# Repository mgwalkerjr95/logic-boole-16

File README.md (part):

<div align="center">

# Logic Boole 16

**An open-source logic analyzer on USB 3: 16 channels at 200 MS/s, or 4 at 750 MS/s.**<br>
It runs from one USB-C cable on a computer, or sits on a Raspberry Pi 4 or 5 as a HAT+.

**[Quick start](boards/v1.0.0/docs/quick-start.pdf)** · **[Datasheet](boards/v1.0.0/docs/datasheet.pdf)** · **[Software](software/README.md)** · **[FPGA design](gateware/README.md)** · **[Firmware](firmware/README.md)** · **[Protocol](docs/protocol.md)** · **[Schematic](boards/v1.0.0/hardware/logic-boole-16_revC_schematic.pdf)**

</div>

This repository holds everything for the board: the KiCad project and fabrication files, the FPGA design, the
firmware, and the software for the computer. The picture is a render of the design.

## Board versions

The version is printed on the back of the board. Each version keeps its own documents and design files in
[boards/](boards/). The software, the FPGA design, the firmware and the [protocol](docs/protocol.md) are shared.

| Version | On the back | Thresholds | Documents | Design files |
|---|---|---|---|---|
| **V1.0.0** (November 2026) | REV C · 2026 | 0.3 to 3 V | [Datasheet](boards/v1.0.0/docs/datasheet.pdf) · [Quick start](boards/v1.0.0/docs/quick-start.pdf) · [Schematic](boards/v1.0.0/hardware/logic-boole-16_revC_schematic.pdf) | [boards/v1.0.0/](boards/v1.0.0/) |

## What it does

| Feature | What you get |
|---|---|
| **16 channels at 200 MS/s** | Two pods of 8, a sample every 5 ns. Clocks up to 85 MHz are captured whole on every input |
| **8 channels at 375 MS/s, 4 at 750 MS/s** | A second FPGA design takes fewer channels more often: a sample every 1.33 ns with four, and clocks up to 200 MHz captured whole on every input. It samples and streams, with no trigger |
| **Two logic voltages in one capture** | A separate threshold for each pod, set from 0.3 V to 3 V |
| **A trigger in the FPGA** | Edges, levels, pulses by their length and levels that have lasted, up to four stages in turn, with a trigger input and a trigger output on a header |
| **Glitch filter and capture clock** | A filter for each channel up to 1.25 µs, and sampling on the circuit's own clock up to 50 MHz |
| **Streams to the host** | Samples go over USB 3 as they are taken, not into a small buffer on the board. The longest capture so far is 600 million samples |
| **Protected inputs** | 1 MΩ, with a comparator on every channel, designed for ±25 V |
| **One cable** | Power and data on USB-C, about 1 W |
| **Raspberry Pi HAT+** | Stacks on a Pi 4 or 5 with room for the Pi 5's Active Cooler. The Pi's own I²C, UART and SPI lines can take the place of pod channels, with no leads, once the board's solder jumpers are closed |
| **Nothing to brick** | The board keeps no firmware: the software loads it over USB each time it is plugged in |
| **Decoders, scripts and AI agents** | I²C, SPI and serial in the app, [sigrok](https://sigrok.org)'s decoders from the command line, a Python package, and an MCP server |

## The app

`logicboole` opens the app in your browser: waveforms, a threshold for each pod, the trigger, and decoders
for I²C, SPI and serial that it can find by itself. With a board on USB it opens on an empty scope: press Start.
With no board it shows its own simulated signals, under a strip marked SIMULATED, as in the picture.
`logicboole --fake` runs the whole software with a stand-in for the board.

## Get started

You need a Mac or a Linux computer (a Raspberry Pi 4 or 5 counts), Python 3.9 or later, and a USB 3 cable with
a USB-C plug for the board. A board comes with no cable, leads, spacers or screws.

**1. Install the software**

```sh
brew install pipx libusb    # macOS, with Homebrew
sudo apt install pipx       # Debian, Ubuntu, Raspberry Pi OS: libusb is there already
pipx ensurepath             # once; then open a new terminal window
pipx install logicboole
```

(`pip install logicboole` in a virtual environment does the same.) On Linux, the first `logicboole check` with
the board plugged in prints one line of commands that installs the USB rule, so that the board can be used
without `sudo`: run it once. To update the software later: `pipx upgrade logicboole`. A board that stayed
plugged in meanwhile is loaded with the new firmware and FPGA design by the next command, which says so.

From a copy of this repository nothing needs installing: `./logicboole`, in its top folder, does what
`logicboole` does here.

**2. Plug the board in and check it**

```sh
logicboole check
```

This checks the computer and the board in a few seconds and says what to do about anything that is missing.
The first time it loads a board, the software downloads the FX3's firmware image (about 110 kB), checks it and
keeps it: that once, the computer needs a connection to the internet.

**3. Capture**

```sh
# The app, in your browser
logicboole

# A capture into two files, the app's own and one for PulseView, with a threshold for each pod
logicboole capture bus.lb16 bus.sr --rate 10M --time 2 -a 1.65 -b 0.9

# Wait up to 10 seconds for B0 to fall, and keep the millisecond after it
logicboole capture reset.sr --rate 200M --time 1ms --trigger "B0=f" --timeout 10

# What is on each channel: I2C, SPI, serial, a clock, PWM
logicboole detect bus.lb16

# What a protocol decoder finds in a saved capture
logicboole decode bus.lb16 i2c scl=A1 sda=A0

# Periods, frequencies and pulse lengths
logicboole measure bus.lb16

# Every low pulse on A0 of 500 ns or less (a sample is 100 ns at 10 MS/s), and a picture of a part of the capture
logicboole find bus.lb16 "A0=0 pulse ..500ns"
logicboole plot bus.lb16 --from 1ms --to 1.2ms
```

While the board waits for its trigger, `capture` prints
`Waiting for the trigger (B0=f), 10 s at the most.  Ctrl-C stops.` Ctrl-C ends the wait early. If the trigger
does not come, the file holds the last samples the board saw, the command says `NOT TRIGGERED`, and it exits with
status 3.

Captures are saved for PulseView (`.sr`), a waveform viewer (`.vcd`), a spreadsheet (`.csv`), or as the app's own
`.lb16`; the commands that read captures read `.lb16` and `.sr`. The decoders are sigrok's, more than a hundred of
them, run through `sigrok-cli` if it is installed. When something does not work,
[docs/troubleshooting.md](docs/troubleshooting.md) goes through what to check. For help, write to
support@nearfieldsupply.com, or open an issue at https://github.com/mgwalkerjr95/logic-boole-16/issues.

> [!TIP]
> The [quick start guide](boards/v1.0.0/docs/quick-start.pdf) goes from the box to a first capture on two pages: where the
> cable and the probes go, and the steps in order. Connect ground first: join any pin of a pod's lower row to
> your circuit's ground.

**Scripts and AI agents.** `import logicboole` is a Python package that needs only libusb, and the commands
print JSON with `--json`. An AI agent can use the board by itself: through the command line with the skill file
(`logicboole skill --install` puts it where Claude Code finds it), or through `logicboole mcp`, a Model Context
Protocol server.
[software/README.md](software/README.md) has every command, the triggers, the Python package, and setting up
an agent.

## Specifications

The [datasheet](boards/v1.0.0/docs/datasheet.pdf) has the full tables, the pins, the dimensions and the limits.

| Item | Value |
|---|---|
| Channels | 16, in two keyed 2 × 8 pods. Every even pin is a ground |
| Sample rate | 200 MS/s on 16 channels, or 200 MS/s divided by a whole number. With the fast FPGA design: 375 MS/s on 8 channels (a pod), 750 MS/s on 4 |
| Fastest signal | Clocks up to 85 MHz and pulses down to 6 ns at 200 MS/s; clocks up to 200 MHz and pulses down to 2.5 ns at 750 MS/s |
| Logic levels | 1.2 to 5 V. Captured so far: 3.3 V and 5 V logic |
| Thresholds | 0.3 to 3.0 V in 0.764 mV steps, one for each pod |
| Inputs | 1 MΩ and 10 pF to ground, designed for ±25 V |
| Streaming, run-length format | 16 channels at 200 MS/s, for signals that change in up to 96 million samples a second |
| Streaming, raw format | 16 channels at 100 MS/s, any signal. At 200 MS/s, 892,928 samples. With the fast design, any signal: 4 channels at 750 MS/s, 8 at 375 or 16 at 187.5 |
| Before the trigger | The newest 8184 words: 16,368 samples in the raw format, far more on quiet signals |
| Trigger header | TRIG IN, and TRIG OUT 75 to 80 ns after the trigger sample |
| Host link | USB 3 at 5 Gbit/s. USB 2.0 works and carries a ninth as much |
| Power | 5 V from USB-C or the Pi's header, about 1 W |
| Size | 82 × 86 mm, four layers, parts on the top side only |
| Main parts | Spartan-6 XC6SLX9 FPGA, Infineon EZ-USB FX3, 16 fast comparators |

## Documentation

| Document | What is in it |
|---|---|
| [Quick start guide](boards/v1.0.0/docs/quick-start.pdf) | From the box to a first capture, on two pages |
| [Datasheet](boards/v1.0.0/docs/datasheet.pdf) | Specifications, pins, dimensions, typical uses, what has been measured and the known limits |
| [Software](software/README.md) | Every command, the triggers, file formats, the Python package, AI agents |
| [FPGA design](gateware/README.md) | What the design does, simulating it, building it, and the published bitstream |
| [Firmware](firmware/README.md) | Building the FX3's firmware, and where the firmware image comes from |
| [Troubleshooting](docs/troubleshooting.md) | What to check when the board is not found, a channel shows nothing, or a capture overflows |
| [Protocol](docs/protocol.md) | The USB requests, the FPGA's registers and the format of the sample stream |
| [Schematic](boards/v1.0.0/hardware/logic-boole-16_revC_schematic.pdf) | Eight sheets, as a PDF |

## What is here

| Path | What it is |
|---|---|
| `logicboole` | Runs the host software from this folder |
| `software/` | The host software: the app, the command line, the Python package, and the skill file and MCP server for AI agents, with the FPGA bitstream they load |
| `gateware/` | The FPGA's design in Verilog, its simulation, and the script that builds it with ISE 14.7 |
| `firmware/` | The FX3's firmware in C, built against Infineon's FX3 SDK |
| `docs/` | The protocol, troubleshooting, and the pictures on this page |
| `boards/` | A folder for each board version. What is in one: |
| `boards/v1.0.0/docs/` | The quick start guide and the datasheet, each as a PDF and as the page it is printed from |
| `boards/v1.0.0/hardware/kicad/` | The KiCad 10 project: schematic (8 sheets), board, design rules, and the symbols and two footprints that are not in KiCad's own libraries |
| `boards/v1.0.0/hardware/bom.csv` | Parts list: maker's part numbers, LCSC numbers, alternatives, and price and stock on the date given |
| `boards/v1.0.0/hardware/fabrication/` | Gerber and drill files (also zipped), and the parts list and placement file for JLCPCB |
| `boards/v1.0.0/hardware/3d/` | 3D model of the assembled board |
| `boards/v1.0.0/hardware/images/` | Renders of the [front](boards/v1.0.0/hardware/images/front.jpg) and the [back](boards/v1.0.0/hardware/images/back.jpg) |

## Changing it

- **The app and the command line** are plain Python and JavaScript with no build step: edit and run.
  [software/README.md](software/README.md) says what is in each file.
- **The FPGA's design** is simulated with Icarus Verilog (`sh gateware/sim.sh`) and built with ISE 14.7.
- **The firmware** is one C file, built with `make` against Infineon's SDK.
- **The hardware**: open `boards/v1.0.0/hardware/kicad/logic-boole-16.kicad_pro` in KiCad 10. The project carries its own
  symbol and footprint libraries; everything else comes from the libraries KiCad installs.
- `./logicboole load --gateware FILE.bin --firmware FILE.img` runs your build on the board, and
  `./logicboole selftest` then checks the path from the FPGA to the computer, every word compared. Nothing you
  load can brick the board: unplug it and plug it in again, and it is as it was.

## Making boards

<details>
<summary><b>Having boards made</b>: the stack-up, what the assembler places, and what is soldered by hand</summary>

<br>

The fabrication files are the ones V1.0.0 (revision C) was made from at JLCPCB.

**Bare board**

| Option | Value |
|---|---|
| Layers, thickness | 4 layers, 1.6 mm |
| Stack-up | JLC04161H-3313. The 90 Ω USB pairs and the 50 Ω lines are sized for it; another stack-up changes their impedance |
| Copper | 1 oz outer, 0.5 oz inner |
| Surface finish | ENIG, for the 0.8 mm BGA and the 0.5 mm pitch parts |
| Smallest features | 0.1 mm track and gap; vias with a 0.2 mm hole in a 0.45 mm pad |

**Assembly**

- Standard assembly, top side only. JLCPCB places 410 parts of 70 types.
- The FX3 (U12) is a BGA and needs X-ray inspection.
- JLCPCB leaves two matched lines unticked, and the boards come without them unless they are ticked: J1, the
  USB-C receptacle, and U3 and U4, the TPS62A02P regulators.
- Check stock of the input ESD diodes (ESD701DPYR, 16 a board) before ordering more than a few boards.

**By hand afterwards**

- J8, the 40-pin stacking header, is not in JLCPCB's library. It is a SparkFun PRT-16764, soldered square to
  the board after delivery.
- On a Raspberry Pi the board sits on four M2.5 × 16 mm spacers, held by eight M2.5 × 6 mm screws, which leaves
  room for the Pi 5's Active Cooler. Spacers and screws are not part of the board.

</details>

<details>
<summary><b>Parts notes</b>: the comparators, the positions left empty, and the programming connectors</summary>

<br>

- **Comparators.** U15 to U18, on pod A, are MX3502S; U19 to U22, on pod B, are TLV3502AIDR. The two parts are
  pin-compatible and either fits all eight positions. JLCPCB draws them a quarter turn apart, so check their
  rotation in the placement preview after changing one.
- **Positions left empty.** U13 takes an SPI flash and J3 a header for the FX3's serial port. They and a few
  resistors are marked "not fitted" in the parts list.
- **Programming connectors.** J2 (FX3) and J4 (FPGA) are Tag-Connect TC2050 footprints for the TC2050-IDC cable.
  They take no part.

</details>

## License

Copyright © 2026 Michael Walker.

| Part | License | Text |
|---|---|---|
| `boards/`, `gateware/`, `docs/`, and whatever is not named below | CERN-OHL-S v2 | [LICENSE](LICENSE) |
| `software/` and the `logicboole` launcher | GPL-3.0-or-later | [software/LICENSE](software/LICENSE) |
| `firmware/` | MIT | [firmware/LICENSE](firmware/LICENSE) |

**The hardware design and the FPGA design.** This source describes Open Hardware and is licensed under the
CERN-OHL-S v2. You may redistribute and modify this source and make products using it under the terms of the
CERN-OHL-S v2, in [LICENSE](LICENSE) and at https://ohwr.org/cern_ohl_s_v2.txt.

This source is distributed WITHOUT ANY EXPRESS OR IMPLIED WARRANTY, INCLUDING OF MERCHANTABILITY, SATISFACTORY
QUALITY AND FITNESS FOR A PARTICULAR PURPOSE. Please see the CERN-OHL-S v2 for applicable conditions.

**The host software** is free software: you can redistribute it and/or modify it under the terms of the GNU
General Public License as published by the Free Software Foundation, either version 3 of the License, or (at your
option) any later version. It is distributed in the hope that it will be useful, but WITHOUT ANY WARRANTY; without
even the implied warranty of MERCHANTABILITY or FITNESS FOR A PARTICULAR PURPOSE. See the GNU General Public
License for more details.

**The firmware's source** is under the MIT license.

**Two built files** are loaded into the board, and each comes under the terms of what it is built from, not
under the host software's:

- `software/logicboole/data/gateware.bin` is the FPGA design, built from `gateware/`: CERN-OHL-S v2.
- **The firmware image is not in this repository.** It is built from `firmware/firmware.c` with Infineon's EZ-USB
  FX3 SDK and also holds code of the SDK's libraries, which is Infineon's and stays under the license of
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
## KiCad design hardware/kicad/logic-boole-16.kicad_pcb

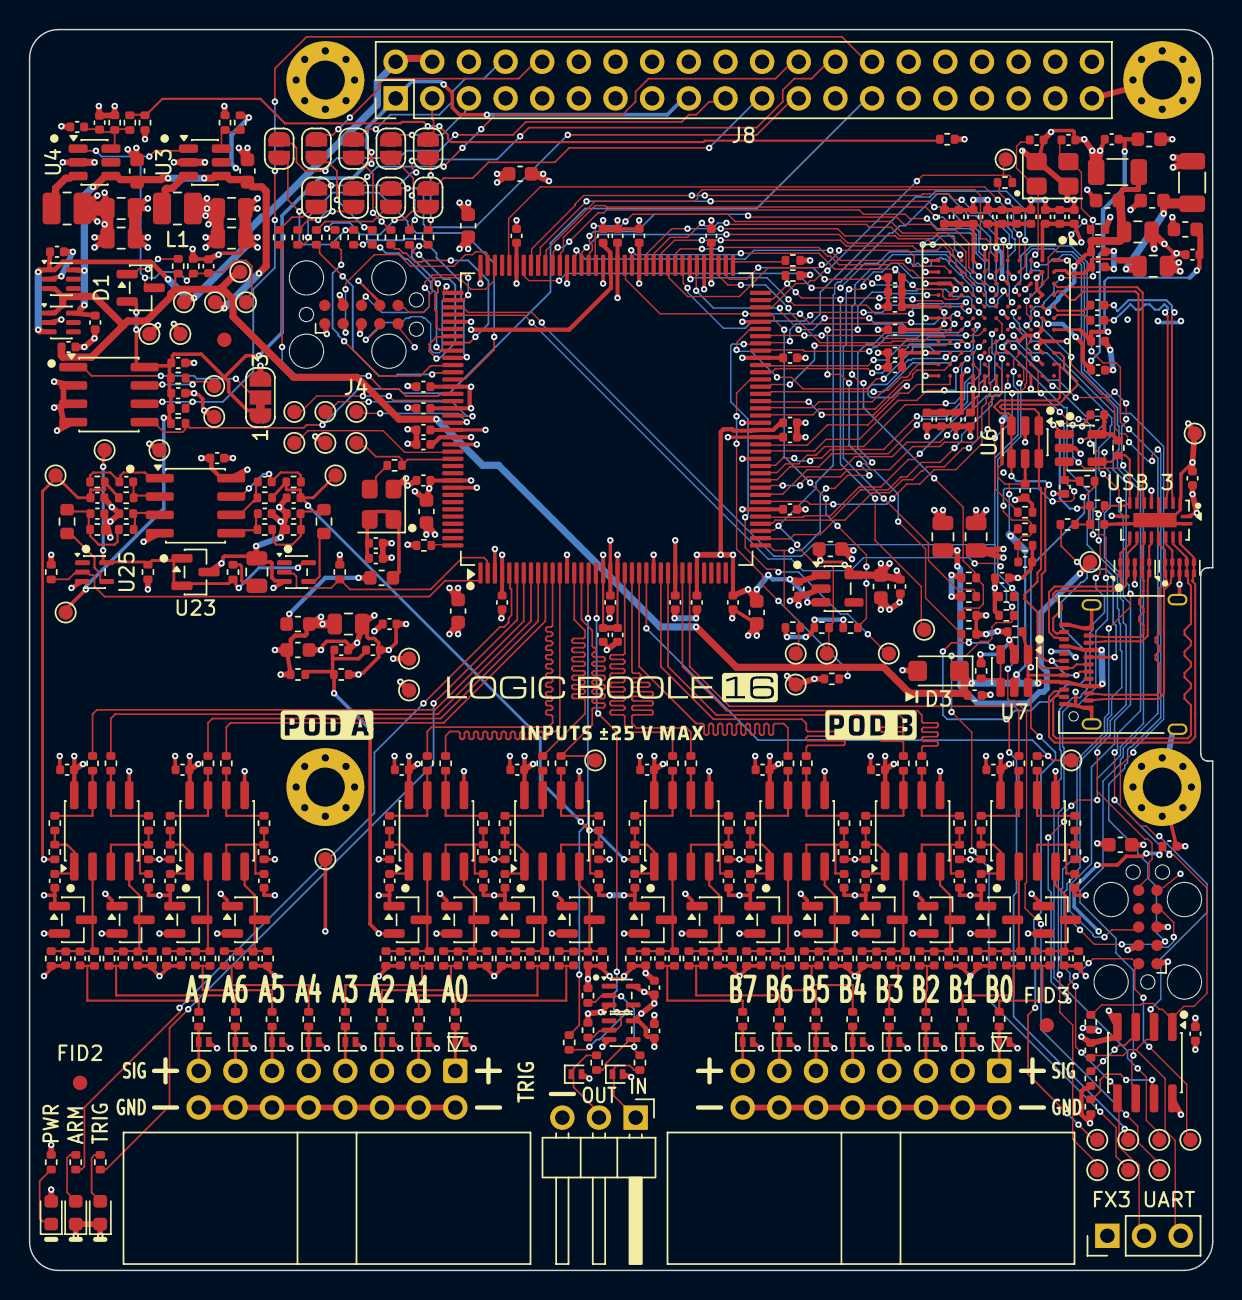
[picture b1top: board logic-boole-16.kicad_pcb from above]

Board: 4 copper layers, 82.0 x 86.0 mm, 477 parts (0 on the bottom side), 283 nets.

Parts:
C1, C10, C15, C58, C61, C90, C120, C154, C158, C159, C164: 1u; C_0402_1005Metric
C2, C12, C14, C18, C19, C20, C21, C24, C25, C26, C27, C28, C29, C35, C38, C41, C42, C44, C45, C47, C49, C51, C53, C55, C59, C60, C94, C101, C108, C115, C124, C131, C138, C145, C150, C151, C152, C155, C156, C160, C161, C162, C163: 100n; C_0402_1005Metric
C3, C16, C17, C30, C31, C32, C33, C43, C46, C48, C50, C52, C54, C153, C157: 10n; C_0402_1005Metric
C4, C7, C11, C62, C68, C74, C78, C82, C85: 4.7u; C_0603_1608Metric
C5, C6, C8, C9, C13, C149: 22u 10V; C_0805_2012Metric
C22, C23: 47u 6.3V; C_0805_2012Metric
C34: 2.2u; C_0402_1005Metric
C36, C39: 100u 6.3V; C_0805_2012Metric
C37, C40: 100u 6.3V; C_1206_3216Metric
C56, C57: 12p C0G; C_0402_1005Metric
C63, C64, C69, C70, C71, C72, C73, C75: 4.7u; C_0402_1005Metric
C65, C66, C67, C76, C77, C79, C80, C81, C83, C84, C86, C87, C88: 470n; C_0402_1005Metric
C89, C119: 10u; C_0603_1608Metric
C91, C95, C98, C102, C105, C109, C112, C116, C121, C125, C128, C132, C135, C139, C142, C146: 4.7p C0G +/-0.1pF; C_0402_1005Metric
C92, C96, C99, C103, C106, C110, C113, C117, C122, C126, C129, C133, C136, C140, C143, C147: 10p C0G 2%; C_0402_1005Metric
C93, C97, C100, C104, C107, C111, C114, C118, C123, C127, C130, C134, C137, C141, C144, C148: 47p C0G 5%; C_0402_1005Metric
C165, C166: 220p; C_0402_1005Metric
D1: BAT54C; SOT-23
D2: green (power); LED_0603_1608Metric
D3: SMF5.0A; D_SMF
D4: yellow (armed); LED_0603_1608Metric
D5: green (triggered / capturing); LED_0603_1608Metric
D6, D8, D10, D12, D14, D16, D18, D20, D22, D24, D26, D28, D30, D32, D34, D36: ESD701DPYR; D_SOD-882
D7, D9, D11, D13, D15, D17, D19, D21, D23, D25, D27, D29, D31, D33, D35, D37: BAV199; SOT-23
D38, D39: H5VL10B; D_SOD-882
FB1, FB2, FB5, FB6: 600R@100MHz; L_0603_1608Metric
FB3, FB4: 120R@100MHz; L_0603_1608Metric
FID1, FID2, FID3: Fiducial; Fiducial_1mm_Mask2mm
H1, H2, H3, H4: M2.5; MountingHole_2.7mm_M2.5_Pad_Via
J1: USB-C 24P (12401610E4#2A); USB_C_Receptacle_Amphenol_12401610E4-2A
J2: Tag-Connect TC2050 (ARM JTAG); Tag-Connect_TC2050-IDC-FP_2x05_P1.27mm_Vertical
J3: UART 1x3 2.54mm; PinHeader_1x03_P2.54mm_Vertical
J4: Tag-Connect TC2050 (Xilinx JTAG); Tag-Connect_TC2050-IDC-FP_2x05_P1.27mm_Vertical
J5: Pod A 2x8 box header (XY-IDC2.54-2*8P-W); IDC-Header_2x08_P2.54mm_Horizontal
J6: Pod B 2x8 box header (XY-IDC2.54-2*8P-W); IDC-Header_2x08_P2.54mm_Horizontal
J7: TRIG 1x3 2.54mm; PinHeader_1x03_P2.54mm_Horizontal
J8: 2x20 stacking header 13.5mm; PinHeader_2x20_P2.54mm_Vertical
JP1: ID addr 0x51 / 0x50; SolderJumper-3_P1.3mm_Bridged12_RoundedPad1.0x1.5mm_NumberL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
JP2: GPIO2 I2C1 SDA; SolderJumper-2_P1.3mm_Open_RoundedPad1.0x1.5mm
JP3: GPIO3 I2C1 SCL; SolderJumper-2_P1.3mm_Open_RoundedPad1.0x1.5mm
JP4: GPIO7 SPI0 CE1; SolderJumper-2_P1.3mm_Open_RoundedPad1.0x1.5mm
JP5: GPIO8 SPI0 CE0; SolderJumper-2_P1.3mm_Open_RoundedPad1.0x1.5mm
JP6: GPIO9 SPI0 MISO; SolderJumper-2_P1.3mm_Open_RoundedPad1.0x1.5mm
JP7: GPIO10 SPI0 MOSI; SolderJumper-2_P1.3mm_Open_RoundedPad1.0x1.5mm
JP8: GPIO11 SPI0 SCLK; SolderJumper-2_P1.3mm_Open_RoundedPad1.0x1.5mm
JP9: GPIO14 UART TXD; SolderJumper-2_P1.3mm_Open_RoundedPad1.0x1.5mm
JP10: GPIO15 UART RXD; SolderJumper-2_P1.3mm_Open_RoundedPad1.0x1.5mm
L1, L2: 1u 4A; L_1008_2520Metric
R1, R2, R10, R11, R137, R143, R152, R155: 100k; R_0402_1005Metric
R3, R12, R16, R17, R18, R19, R20, R22, R23, R24, R140, R142, R146, R148: 10k; R_0402_1005Metric
R4, R26, R27, R149: 2.2k; R_0402_1005Metric
R5, R6, R139, R145: 100k 0.1%; R_0402_1005Metric
R7, R30, R135: 330R; R_0402_1005Metric
R8, R9: 5.1k 1%; R_0402_1005Metric
R13: 10M; R_0402_1005Metric
R14: 6.04k 1%; R_0402_1005Metric
R15: 200R 1%; R_0402_1005Metric
R21: 15k; R_0402_1005Metric
R25: 2k; R_0402_1005Metric
R28, R29, R33: 4.7k; R_0402_1005Metric
R31, R32, R34, R42, R48, R54, R60, R66, R72, R78, R84, R90, R96, R102, R108, R114, R120, R126, R132, R150, R158, R159, R160, R161, R162, R163, R164, R165, R166, R167: 1k; R_0402_1005Metric
R35, R36, R153, R154: 33R; R_0402_1005Metric
R37, R38: 680R; R_0402_1005Metric
R39, R45, R51, R57, R63, R69, R75, R81, R87, R93, R99, R105, R111, R117, R123, R129, R151, R169: 100R; R_0402_1005Metric
R40, R46, R52, R58, R64, R70, R76, R82, R88, R94, R100, R106, R112, R118, R124, R130: 866k 1%; R_0402_1005Metric
R41, R47, R53, R59, R65, R71, R77, R83, R89, R95, R101, R107, R113, R119, R125, R131: 215k 1%; R_0402_1005Metric
R43, R49, R55, R61, R67, R73, R79, R85, R91, R97, R103, R109, R115, R121, R127, R133: 330k; R_0402_1005Metric
R44, R50, R56, R62, R68, R74, R80, R86, R92, R98, R104, R110, R116, R122, R128, R134, R141, R147: 22R; R_0402_1005Metric
R136: 1R 1%; R_0402_1005Metric
R138, R144: 301k 0.1%; R_0603_1608Metric
R156, R157: 3.9k; R_0402_1005Metric
R168: 0R; R_0402_1005Metric
TP1: VBUS; TestPoint_Pad_D1.0mm
TP2: PI_5V; TestPoint_Pad_D1.0mm
TP3: 5V; TestPoint_Pad_D1.0mm
TP4: BUCK_EN; TestPoint_Pad_D1.0mm
TP5: 3V3; TestPoint_Pad_D1.0mm
TP6: 3V3A; TestPoint_Pad_D1.0mm
TP7: 1V8; TestPoint_Pad_D1.0mm
TP8: 1V2; TestPoint_Pad_D1.0mm
TP9: PI_3V3; TestPoint_Pad_D1.0mm
TP10, TP11, TP12, TP30, TP36, TP39: GND; TestPoint_Pad_D1.0mm
TP13: CC1; TestPoint_Pad_D1.0mm
TP14: CC2; TestPoint_Pad_D1.0mm
TP15: SS_SEL; TestPoint_Pad_D1.0mm
TP16: FX3_RST; TestPoint_Pad_D1.0mm
TP17: SCL; TestPoint_Pad_D1.0mm
TP18: SDA; TestPoint_Pad_D1.0mm
TP19: FX3_TRST; TestPoint_Pad_D1.0mm
TP20: PROG_B; TestPoint_Pad_D1.0mm
TP21: INIT_B; TestPoint_Pad_D1.0mm
TP22: CCLK; TestPoint_Pad_D1.0mm
TP23: DIN; TestPoint_Pad_D1.0mm
TP24: DONE; TestPoint_Pad_D1.0mm
TP25: CLK24; TestPoint_Pad_D1.0mm
TP26: DBG0; TestPoint_Pad_D1.0mm
TP27: DBG1; TestPoint_Pad_D1.0mm
TP28: DBG2; TestPoint_Pad_D1.0mm
TP29: DBG3; TestPoint_Pad_D1.0mm
TP31: CHA0; TestPoint_Pad_D1.0mm
TP32: CHB0; TestPoint_Pad_D1.0mm
TP33: VREF; TestPoint_Pad_D1.0mm
TP34: VTH_A; TestPoint_Pad_D1.0mm
TP35: VTH_B; TestPoint_Pad_D1.0mm
TP37: VCLAMP; TestPoint_Pad_D1.0mm
TP38: ID_WP; TestPoint_Pad_D1.0mm
U1, U2: LM66100DCKR; SOT-363_SC-70-6
U3, U4: TPS62A02PDDCR; TSOT-23-6
U5: AP2112K-1.8TRG1; SOT-23-5
U6, U7: USBLC6-2SC6; SOT-23-6
U8, U9: TPD4EUSB30DQAR; USON-10_2.5x1.0mm_P0.5mm
U10: LMV331IDBVR; SOT-23-5
U11: HD3SS3212IRKSR; DHVQFN-20-1EP_2.5x4.5mm_P0.5mm_EP1x3mm
U12: CYUSB3014-BZXI; TFBGA-121_10x10mm_P0.8mm_FX3
U13: W25Q16JVSNIQ; SOIC-8_3.9x4.9mm_P1.27mm
U14: XC6SLX9-2TQG144C; TQFP-144_20x20mm_P0.5mm
U15, U16, U17, U18: MX3502S; SOIC-8_3.9x4.9mm_P1.27mm
U19, U20, U21, U22: TLV3502AIDR; SOIC-8_3.9x4.9mm_P1.27mm
U23: TL431BIDBZR; SOT-23
U24: TLV9062IDR; SOIC-8_3.9x4.9mm_P1.27mm
U25, U26, U27, U28: 74LVC1G17GW; SOT-353_SC-70-5
U29: M24C64-RMN6TP; SOIC-8_3.9x4.9mm_P1.27mm
Y1: 19.2MHz 12pF (X3225192MOB4SI); Crystal_SMD_3225-4Pin_3.2x2.5mm
Y2: 24MHz (OT2EL4C4JI-111OLP-24M); Oscillator_SMD_Abracon_ASE-4Pin_3.2x2.5mm

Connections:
+1V2: C8.1, C9.1, C22.1, C23.1, C24.1, C25.1, C26.1, C27.1, C28.1, C29.1, C30.1, C31.1, C32.1, C33.1, C62.1, C63.1, C64.1, C65.1, C66.1, C67.1, C165.2, FB2.1, FB3.1, FB4.1, L2.2, R168.1, R169.1, TP8.1, U12.B10 (VDD), U12.C3 (VDD), U12.E9 (VDD), U12.F11 (VDD), U12.H1 (VDD), U12.J11 (VDD), U12.L5 (VDD), U12.L7 (VDD), U14.19 (VCCINT), U14.28 (VCCINT), U14.52 (VCCINT), U14.89 (VCCINT), U14.128 (VCCINT)
+1V8: C11.1, C12.1, C44.1, C45.1, C46.1, C47.1, C48.1, C49.1, C50.1, C78.1, C79.1, C80.1, C81.1, C82.1, C83.1, C84.1, R16.1, R18.1, R28.1, R29.1, R30.1, R31.1, R32.1, TP7.1, U5.5 (VOUT), U12.E3 (VIO3), U12.F1 (VIO2), U12.H11 (VIO1), U12.L9 (VIO1), U14.42 (VCCO_2), U14.63 (VCCO_2), U14.76 (VCCO_1), U14.86 (VCCO_1), U14.103 (VCCO_1)
+3V3: C5.1, C6.1, C10.1, C18.1, C19.1, C51.1, C52.1, C53.1, C54.1, C59.1, C68.1, C69.1, C70.1, C71.1, C72.1, C73.1, C74.1, C75.1, C76.1, C77.1, C85.1, C86.1, C87.1, C88.1, C160.1, C161.1, D2.2 (A), FB1.1, FB5.1, FB6.1, J2.1 (VTref), J4.1, L1.2, R3.1, R12.1, R22.1, R23.1, R24.1, R26.1, R27.1, R33.1, TP5.1, U5.1 (VIN), U5.3 (EN), U10.5 (V+), U11.1 (NC/VCC), U11.6 (VCC), U11.10 (NC/VCC), U12.B1 (VIO4), U12.C11 (VIO5), U13.8 (VCC), U14.4 (VCCO_3), U14.18 (VCCO_3), U14.20 (VCCAUX), U14.31 (VCCO_3), U14.36 (VCCAUX), U14.53 (VCCAUX), U14.90 (VCCAUX), U14.122 (VCCO_0), U14.125 (VCCO_0), U14.129 (VCCAUX), U14.135 (VCCO_0), U27.5 (VCC), U28.5 (VCC)
+3V3A: C13.1, C14.1, C89.1, C94.1, C101.1, C108.1, C115.1, C119.1, C124.1, C131.1, C138.1, C145.1, C150.1, FB1.2, R135.1, R149.1, TP6.1, U15.8 (V+), U16.8 (V+), U17.8 (V+), U18.8 (V+), U19.8 (V+), U20.8 (V+), U21.8 (V+), U22.8 (V+), U24.8 (V+)
+5V: C2.1, C4.1, C7.1, TP3.1, U1.6 (VOUT), U2.6 (VOUT), U3.4 (VIN), U4.4 (VIN)
B1V2_FB: C165.1, C166.1, R5.2, R6.1, U4.6 (FB)
B1V2_SNS: R5.1, R168.2, R169.2
B1V2_SW: L2.1, U4.3 (SW)
B3V3_FB: R3.2, R4.1, U3.6 (FB)
B3V3_SW: L1.1, U3.3 (SW)
BUCK_EN: C3.1, D1.3, R2.1, TP4.1, U3.1 (EN), U4.1 (EN)
CC1_F: C16.1, R10.2, U10.3 (-)
CC2_F: C17.1, R11.2, R13.2, U10.1 (+)
CHA0: R44.2, TP31.1, U14.15 (IO_L44P_GCLK21_3)
CHA1: R50.2, U14.14 (IO_L44N_GCLK20_3)
CHA2: R56.2, U14.12 (IO_L49P_3)
CHA3: R62.2, U14.11 (IO_L49N_3)
CHA4: R68.2, U14.10 (IO_L50P_3)
CHA5: R74.2, U14.9 (IO_L50N_3)
CHA6: R80.2, U14.8 (IO_L51P_3)
CHA7: R86.2, U14.7 (IO_L51N_3)
CHB0: R92.2, TP32.1, U14.24 (IO_L41P_GCLK27_3)
CHB1: R98.2, U14.30 (IO_L36P_3)
CHB2: R104.2, U14.29 (IO_L36N_3)
CHB3: R110.2, U14.27 (IO_L37P_3)
CHB4: R116.2, U14.26 (IO_L37N_3)
CHB5: R122.2, U14.23 (IO_L41N_GCLK26_3)
CHB6: R128.2, U14.22 (IO_L42P_GCLK25_TRDY2_3)
CHB7: R134.2, U14.21 (IO_L42N_GCLK24_3)
CLK24: R36.2, TP25.1, U14.132 (IO_L35P_GCLK17_0)
CO_A0: R43.1, R44.1, U15.6 (OUTB)
CO_A1: R49.1, R50.1, U15.7 (OUTA)
CO_A2: R55.1, R56.1, U16.6 (OUTB)
CO_A3: R61.1, R62.1, U16.7 (OUTA)
CO_A4: R67.1, R68.1, U17.6 (OUTB)
CO_A5: R73.1, R74.1, U17.7 (OUTA)
CO_A6: R79.1, R80.1, U18.6 (OUTB)
CO_A7: R85.1, R86.1, U18.7 (OUTA)
CO_B0: R91.1, R92.1, U19.6 (OUTB)
CO_B1: R97.1, R98.1, U19.7 (OUTA)
CO_B2: R103.1, R104.1, U20.6 (OUTB)
CO_B3: R109.1, R110.1, U20.7 (OUTA)
CO_B4: R115.1, R116.1, U21.6 (OUTB)
CO_B5: R121.1, R122.1, U21.7 (OUTA)
CO_B6: R127.1, R128.1, U22.6 (OUTB)
CO_B7: R133.1, R134.1, U22.7 (OUTA)
EN_VBUS: D1.1, R1.2
FLASH_HOLD_N: R23.2, U13.7 (~HOLD/~RESET/IO_{3})
FLASH_WP_N: R22.2, U13.3 (~WP/IO_{2})
FPGA_CCLK: R35.2, TP22.1, U14.70 (IO_L1P_CCLK_2)
FPGA_DBG0: TP26.1, U14.124 (IO_L37P_GCLK13_0)
FPGA_DBG1: TP27.1, U14.126 (IO_L36N_GCLK14_0)
FPGA_DBG2: TP28.1, U14.127 (IO_L36P_GCLK15_0)
FPGA_DBG3: TP29.1, U14.131 (IO_L35N_GCLK16_0)
FPGA_DIN: TP23.1, U12.D2 (I2S_SD/GPIO51), U14.65 (IO_L3P_D0_DIN_MISO_MISO1_2)
FPGA_DONE: R30.2, TP24.1, U12.K5 (CTL10/GPIO27), U14.71 (DONE_2)
FPGA_HSWAPEN: R33.2, U14.144 (IO_L1P_HSWAPEN_0)
FPGA_INIT_B: R29.2, TP21.1, U12.F2 (GPIO45), U14.39 (IO_L65P_INIT_B_2)
FPGA_M0: R31.2, U14.69 (IO_L1N_M0_CMPMISO_2)
FPGA_M1: R32.2, U14.60 (IO_L13P_M1_2)
FPGA_PROGRAM_B: R28.2, TP20.1, U12.H6 (CTL9/GPIO26), U14.37 (PROGRAM_B_2)
FPGA_SUSPEND: R34.1, U14.73 (SUSPEND)
FPGA_TCK: J4.4, U14.109 (TCK)
FPGA_TDI: J4.8, U14.110 (TDI)
FPGA_TDO: J4.6, U14.106 (TDO)
FPGA_TMS: J4.2, U14.107 (TMS)
FX3_AVDD: C34.1, C35.1, FB2.2, U12.A7 (AVDD)
FX3_CTL0: U12.K8 (CTL0/GPIO17), U14.59 (IO_L13N_D10_2)
FX3_CTL1: U12.K7 (CTL1/GPIO18), U14.66 (IO_L2N_CMPMOSI_2)
FX3_CTL2: U12.J7 (CTL2/GPIO19), U14.75 (IO_L74P_AWAKE_1)
FX3_CTL3: U12.H7 (CTL3/GPIO20), U14.67 (IO_L2P_CMPCLK_2)
FX3_CTL4: U12.G7 (CTL4/GPIO21), U14.64 (IO_L3N_MOSI_CSI_B_MISO0_2)
FX3_CTL5: U12.G6 (CTL5/GPIO22), U14.74 (IO_L74N_DOUT_BUSY_1)
FX3_CTL6: U12.K6 (CTL6/GPIO23), U14.78 (IO_L47N_1)
FX3_CTL7: U12.H8 (CTL7/GPIO24), U14.62 (IO_L12P_D1_MISO2_2)
FX3_CTL8: U12.G5 (CTL8/GPIO25), U14.95 (IO_L40P_GCLK11_1)
FX3_CTL11: U12.J5 (CTL11/GPIO28), U14.80 (IO_L46N_1)
FX3_CTL12: U12.H5 (CTL12/GPIO29), U14.79 (IO_L47P_1)
FX3_CVDDQ: C42.1, C43.1, FB5.2, U12.B6 (CVDDQ)
FX3_DQ0: U12.F10 (DQ0/GPIO0), U14.38 (IO_L65N_CSO_B_2)
FX3_DQ1: U12.F9 (DQ1/GPIO1), U14.40 (IO_L64N_D9_2)
FX3_DQ2: U12.F7 (DQ2/GPIO2), U14.44 (IO_L62P_D5_2)
FX3_DQ3: U12.G10 (DQ3/GPIO3), U14.43 (IO_L62N_D6_2)
FX3_DQ4: U12.G9 (DQ4/GPIO4), U14.46 (IO_L49P_D3_2)
FX3_DQ5: U12.F8 (DQ5/GPIO5), U14.41 (IO_L64P_D8_2)
FX3_DQ6: U12.H10 (DQ6/GPIO6), U14.45 (IO_L49N_D4_2)
FX3_DQ7: U12.H9 (DQ7/GPIO7), U14.47 (IO_L48N_RDWR_B_VREF_2)
FX3_DQ8: U12.J10 (DQ8/GPIO8), U14.50 (IO_L31N_GCLK30_D15_2)
FX3_DQ9: U12.J9 (DQ9/GPIO9), U14.58 (IO_L14P_D11_2)
FX3_DQ10: U12.K11 (DQ10/GPIO10), U14.51 (IO_L31P_GCLK31_D14_2)
FX3_DQ11: U12.L10 (DQ11/GPIO11), U14.56 (IO_L30P_GCLK1_D13_2)
FX3_DQ12: U12.K10 (DQ12/GPIO12), U14.55 (IO_L30N_GCLK0_USERCCLK_2)
FX3_DQ13: U12.K9 (DQ13/GPIO13), U14.57 (IO_L14N_D12_2)
FX3_DQ14: U12.J8 (DQ14/GPIO14), U14.61 (IO_L12N_D2_MISO3_2)
FX3_DQ15: U12.G8 (DQ15/GPIO15), U14.48 (IO_L48P_D7_2)
FX3_DQ16: U12.K2 (DQ16/GPIO33), U14.82 (IO_L45N_1)
FX3_DQ17: U12.J4 (DQ17/GPIO34), U14.87 (IO_L42N_GCLK6_TRDY1_1)
FX3_DQ18: U12.K1 (DQ18/GPIO35), U14.83 (IO_L45P_1)
FX3_DQ19: U12.J2 (DQ19/GPIO36), U14.84 (IO_L43N_GCLK4_1)
FX3_DQ20: U12.J3 (DQ20/GPIO37), U14.81 (IO_L46P_1)
FX3_DQ21: U12.J1 (DQ21/GPIO38), U14.85 (IO_L43P_GCLK5_1)
FX3_DQ22: U12.H2 (DQ22/GPIO39), U14.93 (IO_L41P_GCLK9_IRDY1_1)
FX3_DQ23: U12.H3 (DQ23/GPIO40), U14.92 (IO_L41N_GCLK8_1)
FX3_DQ24: U12.F4 (DQ24/GPIO41), U14.98 (IO_L34P_1)
FX3_DQ25: U12.G2 (DQ25/GPIO42), U14.99 (IO_L33N_1)
FX3_DQ26: U12.G3 (DQ26/GPIO43), U14.94 (IO_L40N_GCLK10_1)
FX3_DQ27: U12.F3 (DQ27/GPIO44), U14.97 (IO_L34N_1)
FX3_DQ28: U12.F5 (DQ28/GPIO46), U14.100 (IO_L33P_1)
FX3_DQ29: U12.E1 (DQ29/GPIO47), U14.101 (IO_L32N_1)
FX3_DQ30: U12.E5 (DQ30/GPIO48), U14.104 (IO_L1N_VREF_1)
FX3_DQ31: U12.E4 (DQ31/GPIO49), U14.102 (IO_L32P_1)
FX3_I2S_CLK: R35.1, U12.D1 (I2S_CLK/GPIO50)
FX3_PCLK: U12.J6 (PCLK/GPIO16), U14.88 (IO_L42P_GCLK7_1)
FX3_PMODE0: R16.2, R17.1, U12.G4 (PMODE0/GPIO30)
FX3_PMODE1: R18.2, U12.H4 (PMODE1/GPIO31)
FX3_PMODE2: R19.1, U12.L4 (PMODE2/GPIO32)
FX3_RESET_N: C58.1, J2.10 (~RESET), R20.2, R21.1, TP16.1, U12.C5 (RESET#)
FX3_RUSB2: R14.1, U12.C8 (R_USB2)
FX3_RUSB3: R15.1, U12.B3 (R_USB3)
FX3_SCL: R26.2, TP17.1, U12.D9 (I2C_GPIO58/I2C_SCL), U14.111 (IO_L66N_SCP0_0)
FX3_SDA: R27.2, TP18.1, U12.D10 (I2C_GPIO59/I2C_SDA), U14.112 (IO_L66P_SCP1_0)
FX3_SPI_MISO: J3.3, R25.1, U12.C2 (UART_TX/SPI_MISO/GPIO55), U13.2 (DO/IO_{1})
FX3_SPI_MOSI: J3.2, U12.D5 (UART_RX/SPI_MOSI/GPIO56), U13.5 (DI/IO_{0})
FX3_SPI_SCK: U12.D4 (UART_RTS/SPI_SCK/GPIO53), U13.6 (CLK)
FX3_SPI_SSN: R24.2, U12.C1 (UART_CTS/SPI_SSN/GPIO54), U13.1 (~CS)
FX3_SSTX_N: C21.1, U12.A6 (SSTXM)
FX3_SSTX_P: C20.1, U12.A5 (SSTXP)
FX3_TCK: J2.4 (SWCLK/TCK), U12.F6 (TCK)
FX3_TDI: J2.8 (NC/TDI), U12.E7 (TDI)
FX3_TDO: J2.6 (SWO/TDO), U12.C10 (TDO)
FX3_TMS: J2.2 (SWDIO/TMS), U12.E8 (TMS)
FX3_TRST_N: TP19.1, U12.B11 (TRST#)
FX3_U3RX: C39.1, C40.1, C41.1, FB4.2, U12.A2 (U3RXVDDQ)
FX3_U3TX: C36.1, C37.1, C38.1, FB3.2, U12.B5 (U3TXVDDQ)
FX3_XI: C56.1, U12.C6 (XTALIN), Y1.1
FX3_XO: C57.1, U12.C7 (XTALOUT), Y1.3
GND: C1.2, C2.2, C3.2, C4.2, C5.2, C6.2, C7.2, C8.2, C9.2, C10.2, C11.2, C12.2, C13.2, C14.2, C15.2, C16.2, C17.2, C18.2, C19.2, C22.2, C23.2, C24.2, C25.2, C26.2, C27.2, C28.2, C29.2, C30.2, C31.2, C32.2, C33.2, C34.2, C35.2, C36.2, C37.2, C38.2, C39.2, C40.2, C41.2, C42.2, C43.2, C44.2, C45.2, C46.2, C47.2, C48.2, C49.2, C50.2, C51.2, C52.2, C53.2, C54.2, C55.2, C56.2, C57.2, C58.2, C59.2, C60.2, C61.2, C62.2, C63.2, C64.2, C65.2, C66.2, C67.2, C68.2, C69.2, C70.2, C71.2, C72.2, C73.2, C74.2, C75.2, C76.2, C77.2, C78.2, C79.2, C80.2, C81.2, C82.2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
ID_A0: JP1.2 (C), U29.1 (A0)
ID_SC: J8.28, R157.2, U29.6 (SCL)
ID_SD: J8.27, R156.2, U29.5 (SDA)
ID_WP: R158.2, TP38.1, U29.7 (WP)
INS_A0: C91.1, R39.2, R40.1
INS_A1: C95.1, R45.2, R46.1
INS_A2: C98.1, R51.2, R52.1
INS_A3: C102.1, R57.2, R58.1
INS_A4: C105.1, R63.2, R64.1
INS_A5: C109.1, R69.2, R70.1
INS_A6: C112.1, R75.2, R76.1
INS_A7: C116.1, R81.2, R82.1
INS_B0: C121.1, R87.2, R88.1
INS_B1: C125.1, R93.2, R94.1
INS_B2: C128.1, R99.2, R100.1
INS_B3: C132.1, R105.2, R106.1
INS_B4: C135.1, R111.2, R112.1
INS_B5: C139.1, R117.2, R118.1
INS_B6: C142.1, R123.2, R124.1
INS_B7: C146.1, R129.2, R130.1
IN_A0: D6.1 (A1), J5.1, R39.1
IN_A1: D8.1 (A1), J5.3, R45.1
IN_A2: D10.1 (A1), J5.5, R51.1
IN_A3: D12.1 (A1), J5.7, R57.1
IN_A4: D14.1 (A1), J5.9, R63.1
IN_A5: D16.1 (A1), J5.11, R69.1
IN_A6: D18.1 (A1), J5.13, R75.1
IN_A7: D20.1 (A1), J5.15, R81.1
IN_B0: D22.1 (A1), J6.1, R87.1
IN_B1: D24.1 (A1), J6.3, R93.1
IN_B2: D26.1 (A1), J6.5, R99.1
IN_B3: D28.1 (A1), J6.7, R105.1
IN_B4: D30.1 (A1), J6.9, R111.1
IN_B5: D32.1 (A1), J6.11, R117.1
IN_B6: D34.1 (A1), J6.13, R123.1
IN_B7: D36.1 (A1), J6.15, R129.1
LED_ARM: R37.1, U14.5 (IO_L52N_3)
LED_ARM_A: D4.2 (A), R37.2
LED_TRIG: R38.1, U14.6 (IO_L52P_3)
LED_TRIG_A: D5.2 (A), R38.2
ND_A0: C91.2, C92.1, D7.3 (COM), R40.2, R41.1, U15.4 (-INB)
ND_A1: C95.2, C96.1, D9.3 (COM), R46.2, R47.1, U15.2 (-INA)
ND_A2: C98.2, C99.1, D11.3 (COM), R52.2, R53.1, U16.4 (-INB)
ND_A3: C102.2, C103.1, D13.3 (COM), R58.2, R59.1, U16.2 (-INA)
ND_A4: C105.2, C106.1, D15.3 (COM), R64.2, R65.1, U17.4 (-INB)
ND_A5: C109.2, C110.1, D17.3 (COM), R70.2, R71.1, U17.2 (-INA)
ND_A6: C112.2, C113.1, D19.3 (COM), R76.2, R77.1, U18.4 (-INB)
ND_A7: C116.2, C117.1, D21.3 (COM), R82.2, R83.1, U18.2 (-INA)
ND_B0: C121.2, C122.1, D23.3 (COM), R88.2, R89.1, U19.4 (-INB)
ND_B1: C125.2, C126.1, D25.3 (COM), R94.2, R95.1, U19.2 (-INA)
ND_B2: C128.2, C129.1, D27.3 (COM), R100.2, R101.1, U20.4 (-INB)
ND_B3: C132.2, C133.1, D29.3 (COM), R106.2, R107.1, U20.2 (-INA)
ND_B4: C135.2, C136.1, D31.3 (COM), R112.2, R113.1, U21.4 (-INB)
ND_B5: C139.2, C140.1, D33.3 (COM), R118.2, R119.1, U21.2 (-INA)
ND_B6: C142.2, C143.1, D35.3 (COM), R124.2, R125.1, U22.4 (-INB)
ND_B7: C146.2, C147.1, D37.3 (COM), R130.2, R131.1, U22.2 (-INA)
PIF_GPIO2: R159.2, U14.114 (IO_L65N_SCP2_0)
PIF_GPIO3: R160.2, U14.115 (IO_L65P_SCP3_0)
PIF_GPIO7: R161.2, U14.123 (IO_L37N_GCLK12_0)
PIF_GPIO8: R162.2, U14.121 (IO_L62P_0)
PIF_GPIO9: R163.2, U14.119 (IO_L63P_SCP7_0)
PIF_GPIO10: R164.2, U14.118 (IO_L63N_SCP6_0)
PIF_GPIO11: R165.2, U14.120 (IO_L62N_VREF_0)
PIF_GPIO14: R166.2, U14.116 (IO_L64N_SCP4_0)
PIF_GPIO15: R167.2, U14.117 (IO_L64P_SCP5_0)
PI_3V3: C162.1, C163.1, D1.2, J8.1, J8.17, JP1.1 (A), R156.1, R157.1, R158.1, TP9.1, U29.8 (VCC)
PI_5V: C1.1, J8.2, J8.4, TP2.1, U1.3 (~CE), U2.1 (VIN)
PI_GPIO2: J8.3, JP2.1 (A)
PI_GPIO2_J: JP2.2 (B), R159.1
PI_GPIO3: J8.5, JP3.1 (A)
PI_GPIO3_J: JP3.2 (B), R160.1
PI_GPIO7: J8.26, JP4.1 (A)
PI_GPIO7_J: JP4.2 (B), R161.1
PI_GPIO8: J8.24, JP5.1 (A)
PI_GPIO8_J: JP5.2 (B), R162.1
PI_GPIO9: J8.21, JP6.1 (A)
PI_GPIO9_J: JP6.2 (B), R163.1
PI_GPIO10: J8.19, JP7.1 (A)
PI_GPIO10_J: JP7.2 (B), R164.1
PI_GPIO11: J8.23, JP8.1 (A)
PI_GPIO11_J: JP8.2 (B), R165.1
PI_GPIO14: J8.8, JP9.1 (A)
PI_GPIO14_J: JP9.2 (B), R166.1
PI_GPIO15: J8.10, JP10.1 (A)
PI_GPIO15_J: JP10.2 (B), R167.1
PWMR_A: R138.1, U25.4
PWMR_B: R144.1, U26.4
PWM_A: R137.1, U14.1 (IO_L83N_VREF_3), U25.2
PWM_B: R143.1, U14.2 (IO_L83P_3), U26.2
PWR_LED_K: D2.1 (K), R7.1
SS_SEL: R12.2, R13.1, TP15.1, U10.4, U11.9 (SEL)
THB_FA: C153.2, R142.2, U24.2 (-INA)
THB_FB: C157.2, R148.2, U24.6 (-INB)
THB_OA: C153.1, R141.1, U24.1 (OUTA)
THB_OB: C157.1, R147.1, U24.7 (OUTB)
THF_A: C151.1, R138.2, R139.1, R140.1
THF_B: C155.1, R144.2, R145.1, R146.1
THN_A: C152.1, R140.2, U24.3 (+INA)
THN_B: C156.1, R146.2, U24.5 (+INB)
TH_A0: C93.1, R42.2, R43.2, U15.3 (+INB)
TH_A1: C97.1, R48.2, R49.2, U15.1 (+INA)
TH_A2: C100.1, R54.2, R55.2, U16.3 (+INB)
TH_A3: C104.1, R60.2, R61.2, U16.1 (+INA)
TH_A4: C107.1, R66.2, R67.2, U17.3 (+INB)
TH_A5: C111.1, R72.2, R73.2, U17.1 (+INA)
TH_A6: C114.1, R78.2, R79.2, U18.3 (+INB)
TH_A7: C118.1, R84.2, R85.2, U18.1 (+INA)
TH_B0: C123.1, R90.2, R91.2, U19.3 (+INB)
TH_B1: C127.1, R96.2, R97.2, U19.1 (+INA)
TH_B2: C130.1, R102.2, R103.2, U20.3 (+INB)
TH_B3: C134.1, R108.2, R109.2, U20.1 (+INA)
TH_B4: C137.1, R114.2, R115.2, U21.3 (+INB)
TH_B5: C141.1, R120.2, R121.2, U21.1 (+INA)
TH_B6: C144.1, R126.2, R127.2, U22.3 (+INB)
TH_B7: C148.1, R132.2, R133.2, U22.1 (+INA)
TRIG_IN: R153.2, U14.16 (IO_L43N_GCLK22_IRDY2_3)
TRIG_IN_B: R151.2, R152.1, U27.2
TRIG_IN_J: D38.1 (A1), J7.1, R151.1
TRIG_IN_Y: R153.1, U27.4
TRIG_OUT: R155.1, U14.17 (IO_L43P_GCLK23_3), U28.2
TRIG_OUT_J: D39.1 (A1), J7.2, R154.2
TRIG_OUT_Y: R154.1, U28.4
USBC_CC1: J1.A5 (CC1), R8.1, R10.1, TP13.1, U7.1 (I/O1), U7.6 (I/O1)
USBC_CC2: J1.B5 (CC2), R9.1, R11.1, TP14.1, U7.3 (I/O2), U7.4 (I/O2)
USBC_D_N: J1.A7 (D-), J1.B7 (D-), U6.3 (I/O2), U6.4 (I/O2), U12.A10 (DM)
USBC_D_P: J1.A6 (D+), J1.B6 (D+), U6.1 (I/O1), U6.6 (I/O1), U12.A9 (DP)
USBC_RX1_N: J1.B10 (RX1-), U8.1 (D1+), U8.10 (NC), U11.16 (B1n)
USBC_RX1_P: J1.B11 (RX1+), U8.2 (D1-), U8.9 (NC), U11.17 (B1p)
USBC_RX2_N: J1.A10 (RX2-), U9.1 (D1+), U9.10 (NC), U11.12 (C1n)
USBC_RX2_P: J1.A11 (RX2+), U9.2 (D1-), U9.9 (NC), U11.13 (C1p)
USBC_TX1_N: J1.A3 (TX1-), U8.5 (D2-), U8.6 (NC), U11.19 (B0p)
USBC_TX1_P: J1.A2 (TX1+), U8.4 (D2+), U8.7 (NC), U11.18 (B0n)
USBC_TX2_N: J1.B3 (TX2-), U9.5 (D2-), U9.6 (NC), U11.15 (C0p)
USBC_TX2_P: J1.B2 (TX2+), U9.4 (D2+), U9.7 (NC), U11.14 (C0n)
USBSS_RX_N: U11.7 (A1p), U12.A3 (SSRXM)
USBSS_RX_P: U11.8 (A1n), U12.A4 (SSRXP)
USBSS_TX_N: C21.2, U11.4 (A0n)
USBSS_TX_P: C20.2, U11.3 (A0p)
VBUS: C15.1, C55.1, C164.1, D3.1 (A1), J1.A4 (VBUS), J1.A9 (VBUS), J1.B4 (VBUS), J1.B9 (VBUS), R1.1, R20.1, TP1.1, U1.1 (VIN), U2.3 (~CE), U6.5 (VBUS), U7.5 (VBUS), U12.E11 (VBUS)
VCLAMP: C90.1, C120.1, C159.1, D7.2 (K), D9.2 (K), D11.2 (K), D13.2 (K), D15.2 (K), D17.2 (K), D19.2 (K), D21.2 (K), D23.2 (K), D25.2 (K), D27.2 (K), D29.2 (K), D31.2 (K), D33.2 (K), D35.2 (K), D37.2 (K), R149.2, R150.1, TP37.1
VREF2V5: R135.2, R136.1, TP33.1, U23.1 (K), U23.2 (REF), U25.5 (VCC), U26.5 (VCC)
VREF_C: C149.1, R136.2
VTH_A: C154.1, R42.1, R48.1, R54.1, R60.1, R66.1, R72.1, R78.1, R84.1, R141.2, R142.1, TP34.1
VTH_B: C158.1, R90.1, R96.1, R102.1, R108.1, R114.1, R120.1, R126.1, R132.1, R147.2, R148.1, TP35.1
XO_OUT: R36.1, Y2.3 (OUT)
XO_VDD: C60.1, C61.1, FB6.2, Y2.1 (EN), Y2.4 (Vdd)

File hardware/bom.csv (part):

MPN,Manufacturer,Value / description,Quantity per board,Distributor,Distributor part number,JLCPCB library,Unit price at 100 boards (USD),Extended price per board (USD),Distributor stock,Date stock checked,References,Notes
CYUSB3014-BZXI,Infineon,CYUSB3014-BZXI,1,JLCPCB / LCSC,C57294,Extended,13.2582,13.26,4835,2026-10-27,U12,
XC6SLX9-2TQG144C,AMD (Xilinx),XC6SLX9-2TQG144C,1,JLCPCB / LCSC,C27408,Extended,5.8582,5.86,1529,2026-10-27,U14,
TLV3502AIDR,Texas Instruments,TLV3502AIDR,4,JLCPCB / LCSC,C131165,Extended,1.4019,5.61,2345,2026-10-28,U19 U20 U21 U22,pod B; pin-compatible with the MX3502S and the COS3502SR
PRT-16764,SparkFun (4UCON drawing 11297),"2x20 female stacking header, 13.5 mm body, 9.8 mm tails (16 mm board-to-board)",1,SparkFun,PRT-16764,,2.9300,2.93,in stock (no count shown),2026-10-21,J8,"LCSC / JLCPCB stock none taller than 8.5 mm; supplied for assembly or fitted by hand; second source Electrokit 41013063 (13.5 mm body, 10.0 mm tails, 243 in stock)"
ESD701DPYR,Texas Instruments,ESD701DPYR,16,JLCPCB / LCSC,C42409125,Extended,0.1374,2.20,150,2026-10-27,D6 D8 D10 D12 D14 D16 D18 D20 D22 D24 D26 D28 D30 D32 D34 D36,JLCPCB stock covers 9 boards; alternatives: ESD701DPYRQ1
HD3SS3212IRKSR,Texas Instruments,HD3SS3212IRKSR,1,JLCPCB / LCSC,C544517,Extended,1.0803,1.08,2441,2026-10-27,U11,alternatives: PI3USB302-AZBEX
MX3502S,Maxinmicro,MX3502S,4,JLCPCB / LCSC,C19269867,Extended,0.2300,0.92,17606,2026-10-27,U15 U16 U17 U18,"pod A; alternatives: COS3502SR, TLV3502AIDR (pin-compatible)"
12401610E4#2A,Amphenol,USB-C 24P (12401610E4#2A),1,JLCPCB / LCSC,C5119948,Extended,0.8888,0.89,6554,2026-10-27,J1,
GRM21BR60J107ME15L,Murata,100u 6.3V,2,JLCPCB / LCSC,C141660,Extended,0.3588,0.72,159970,2026-10-27,C36 C39,alternatives: JMK212BBJ107MG-T
"BAV199,215",Nexperia,BAV199,16,JLCPCB / LCSC,C40919,Extended,0.0259,0.41,67397,2026-10-27,D7 D9 D11 D13 D15 D17 D19 D21 D23 D25 D27 D29 D31 D33 D35 D37,alternatives: BAV199
OT2EL4C4JI-111OLP-24M,YXC,24MHz (OT2EL4C4JI-111OLP-24M),1,JLCPCB / LCSC,C5203548,Extended,0.3520,0.35,3611,2026-10-27,Y2,alternatives: OT322524MJBA4SL
XY-IDC2.54-2*8P-W,XYECONN,Pod A 2x8 box header (XY-IDC2.54-2*8P-W),2,JLCPCB / LCSC,C53200827,Extended,0.1614,0.32,863,2026-10-27,J5 J6,alternatives: 2.54-2*8P
"74LVC1G17GW,125",Nexperia,74LVC1G17GW,4,JLCPCB / LCSC,C426705,Extended,0.0753,0.30,15198,2026-10-27,U25 U26 U27 U28,alternatives: 74LVC1G17GW
LM66100DCKR,Texas Instruments,LM66100DCKR,2,JLCPCB / LCSC,C2869734,Extended,0.1482,0.30,16902,2026-10-27,U1 U2,
TPS62A02PDDCR,Texas Instruments,TPS62A02PDDCR,2,JLCPCB / LCSC,C22445521,Extended,0.1244,0.25,3524,2026-10-27,U3 U4,
USBLC6-2SC6,STMicroelectronics,USBLC6-2SC6,2,JLCPCB / LCSC,C7519,Extended,0.1181,0.24,34987,2026-10-27,U6 U7,
CL21A226MPQNNNE,Samsung,22u 10V,6,JLCPCB / LCSC,C29277,Extended,0.0300,0.18,113738,2026-10-27,C5 C6 C8 C9 C13 C149,"alternatives: CL21A226MAQNNNE, GRM21BR61A226ME44L"
CL31A107MQHNNNE,Samsung,100u 6.3V,2,JLCPCB / LCSC,C15008,Basic,0.0860,0.17,1875640,2026-10-27,C37 C40,alternatives: GRM31CR60J107ME39L
CL21A476MQYNNNE,Samsung,47u 6.3V,2,JLCPCB / LCSC,C16780,Basic,0.0798,0.16,1089967,2026-10-27,C22 C23,alternatives: GRM21BR60J476ME15L
M24C64-RMN6TP,STMicroelectronics,M24C64-RMN6TP,1,JLCPCB / LCSC,C79988,Preferred,0.1456,0.15,180165,2026-10-27,U29,
AP2112K-1.8TRG1,Diodes Inc.,AP2112K-1.8TRG1,1,JLCPCB / LCSC,C176944,Extended,0.1334,0.13,33293,2026-10-27,U5,
TPD4EUSB30DQAR-N,BORN,TPD4EUSB30DQAR,2,JLCPCB / LCSC,C5148477,Extended,0.0636,0.13,22900,2026-10-27,U8 U9,alternatives: TPD4EUSB30DQAR
CL05A474KP5NNNC,Samsung,470n,13,JLCPCB / LCSC,C47339,Preferred,0.0097,0.13,745772,2026-10-27,C65 C66 C67 C76 C77 C79 C80 C81 C83 C84 C86 C87 C88,alternatives: CL05A474KA5NNNC
RT0402BRD07100KL,YAGEO,100k 0.1%,4,JLCPCB / LCSC,C852472,Extended,0.0256,0.10,1006736,2026-10-27,R5 R6 R139 R145,"alternatives: ERA-2AEB1003X, RG1005P-1003-B-T5, AR02BTC1003, TNPW0402100KBEED, RT0402BRE07100KL"
CL10A475KO8NNNC,Samsung,4.7u,9,JLCPCB / LCSC,C19666,Basic,0.0109,0.10,3348930,2026-10-27,C4 C7 C11 C62 C68 C74 C78 C82 C85,alternatives: GRM188R61C475KAAJD
CL05B104KO5NNNC,Samsung,100n,42,JLCPCB / LCSC,C1525,Basic,0.0023,0.10,34135642,2026-10-27,C2 C12 C14 C18 C19 C20 C21 C24 C25 C26 C27 C28 C29 C35 C38 C41 C42 C44 C45 C47 C49 C51 C53 C55 C59 C60 C94 C101 C108 C115 C124 C131 C138 C145 C150 C151 C152 C155 C156 C160 C161 C162 C163,1 not fitted; alternatives: GRM155R71C104KA88D
TLV9062IDR,Texas Instruments,TLV9062IDR,1,JLCPCB / LCSC,C398355,Extended,0.0943,0.09,196864,2026-10-27,U24,
CL05A475MP5NRNC,Samsung,4.7u,8,JLCPCB / LCSC,C23733,Basic,0.0117,0.09,2524175,2026-10-28,C63 C64 C69 C70 C71 C72 C73 C75,alternatives: GRM155R61A475MEAAD
LMV331IDBVR,Texas Instruments,LMV331IDBVR,1,JLCPCB / LCSC,C34731,Extended,0.0894,0.09,171803,2026-10-27,U10,
X3225192MOB4SI,YXC,19.2MHz 12pF (X3225192MOB4SI),1,JLCPCB / LCSC,C411225,Extended,0.0871,0.09,790,2026-10-27,Y1,
BLM18KG601SN1D,Murata,600R@100MHz,4,JLCPCB / LCSC,C85833,Extended,0.0182,0.07,195075,2026-10-27,FB1 FB2 FB5 FB6,
CC0402GRNPO9BN100,YAGEO,10p C0G 2%,16,JLCPCB / LCSC,C325459,Extended,0.0041,0.07,17772,2026-10-27,C92 C96 C99 C103 C106 C110 C113 C117 C122 C126 C129 C133 C136 C140 C143 C147,"alternatives: GRM1555C1H100GA01D, 0402CG100G500NT"
RT0603BRD07301KL,YAGEO,301k 0.1%,2,JLCPCB / LCSC,C861309,Extended,0.0325,0.07,12675,2026-10-27,R138 R144,alternatives: RT0603BRE07301KL
FTC252012S1R0MBCA,Changjiang Microelectronics,1u 4A,2,JLCPCB / LCSC,C5832370,Extended,0.0284,0.06,367300,2026-10-27,L1 L2,
0402CG470J500NT,FH,47p C0G 5%,16,JLCPCB / LCSC,C1567,Basic,0.0035,0.06,628689,2026-10-27,C93 C97 C100 C104 C107 C111 C114 C118 C123 C127 C130 C134 C137 C141 C144 C148,"alternatives: GRM1555C1H470JA01D, CL05C470JB5NNNC"
TL431BIDBZR,Texas Instruments,TL431BIDBZR,1,JLCPCB / LCSC,C41283,Extended,0.0550,0.06,163957,2026-10-27,U23,
CL05A105KA5NQNC,Samsung,1u,11,JLCPCB / LCSC,C52923,Basic,0.0049,0.05,11180807,2026-10-27,C1 C10 C15 C58 C61 C90 C120 C154 C158 C159 C164,alternatives: GRM155R61A105KE15D
CC0402BRNPO9BN4R7,YAGEO,4.7p C0G +/-0.1pF,16,JLCPCB / LCSC,C325453,Extended,0.0033,0.05,805339,2026-10-27,C91 C95 C98 C102 C105 C109 C112 C116 C121 C125 C128 C132 C135 C139 C142 C146,"alternatives: GJM1555C1H4R7BB01D, 0402CG4R7B500NT"
CL05B103KB5NNNC,Samsung,10n,15,JLCPCB / LCSC,C15195,Basic,0.0029,0.04,6600770,2026-10-27,C3 C16 C17 C30 C31 C32 C33 C43 C46 C48 C50 C52 C54 C153 C157,alternatives: GRM155R71H103KA88D
CL10A106KP8NNNC,Samsung,10u,2,JLCPCB / LCSC,C19702,Basic,0.0202,0.04,12520973,2026-10-27,C89 C119,alternatives: GRM188R61A106KE69D
BLM18PG121SN1D,Murata,120R@100MHz,2,JLCPCB / LCSC,C14709,Basic,0.0152,0.03,2687578,2026-10-27,FB3 FB4,
0402WGF1001TCE,UNI-ROYAL,1k,30,JLCPCB / LCSC,C11702,Basic,0.0010,0.03,18384345,2026-10-27,R31 R32 R34 R42 R48 R54 R60 R66 R72 R78 R84 R90 R96 R102 R108 R114 R120 R126 R132 R150 R158 R159 R160 R161 R162 R163 R164 R165 R166 R167,alternatives: RC0402FR-071KL
SMF5.0A,Hongjiacheng,SMF5.0A,1,JLCPCB / LCSC,C19077497,Preferred,0.0284,0.03,917656,2026-10-27,D3,
PZ254R-11-03P,XFCN,TRIG 1x3 2.54mm,1,JLCPCB / LCSC,C492411,Extended,0.0244,0.02,49302,2026-10-27,J7,alternatives: XY-PZ254R-11-03P
0402WGF8663TCE,UNI-ROYAL,866k 1%,16,JLCPCB / LCSC,C27020,Extended,0.0015,0.02,7357,2026-10-27,R40 R46 R52 R58 R64 R70 R76 R82 R88 R94 R100 R106 R112 R118 R124 R130,alternatives: RC0402FR-07866KL
KT-0603G,Hubei KENTO,green (power),2,JLCPCB / LCSC,C12624,Extended,0.0117,0.02,437736,2026-10-27,D2 D5,alternatives: 19-217/GHC-YR1S2/3T
0402WGF220JTCE,UNI-ROYAL,22R,18,JLCPCB / LCSC,C25092,Basic,0.0012,0.02,3130393,2026-10-27,R44 R50 R56 R62 R68 R74 R80 R86 R92 R98 R104 R110 R116 R122 R128 R134 R141 R147,alternatives: RC0402FR-0722RL
NCD0603Y2,NationStar,yellow (armed),1,JLCPCB / LCSC,C89811,Preferred,0.0197,0.02,185865,2026-10-27,D4,alternatives: KT-0603Y
0402WGF2153TCE,UNI-ROYAL,215k 1%,16,JLCPCB / LCSC,C11489,Extended,0.0012,0.02,40838,2026-10-27,R41 R47 R53 R59 R65 R71 R77 R83 R89 R95 R101 R107 R113 R119 R125 R131,alternatives: RC0402FR-07215KL
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

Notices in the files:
README.md:
Hardware: CERN-OHL-S v2
Software: GPL-3.0-or-later
The fonts in `boards/v1.0.0/docs/datasheet/fonts/` are other people's work, each under the SIL Open Font License:
